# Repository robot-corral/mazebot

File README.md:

# mazebot
robot which sole purpose is to escape a maze

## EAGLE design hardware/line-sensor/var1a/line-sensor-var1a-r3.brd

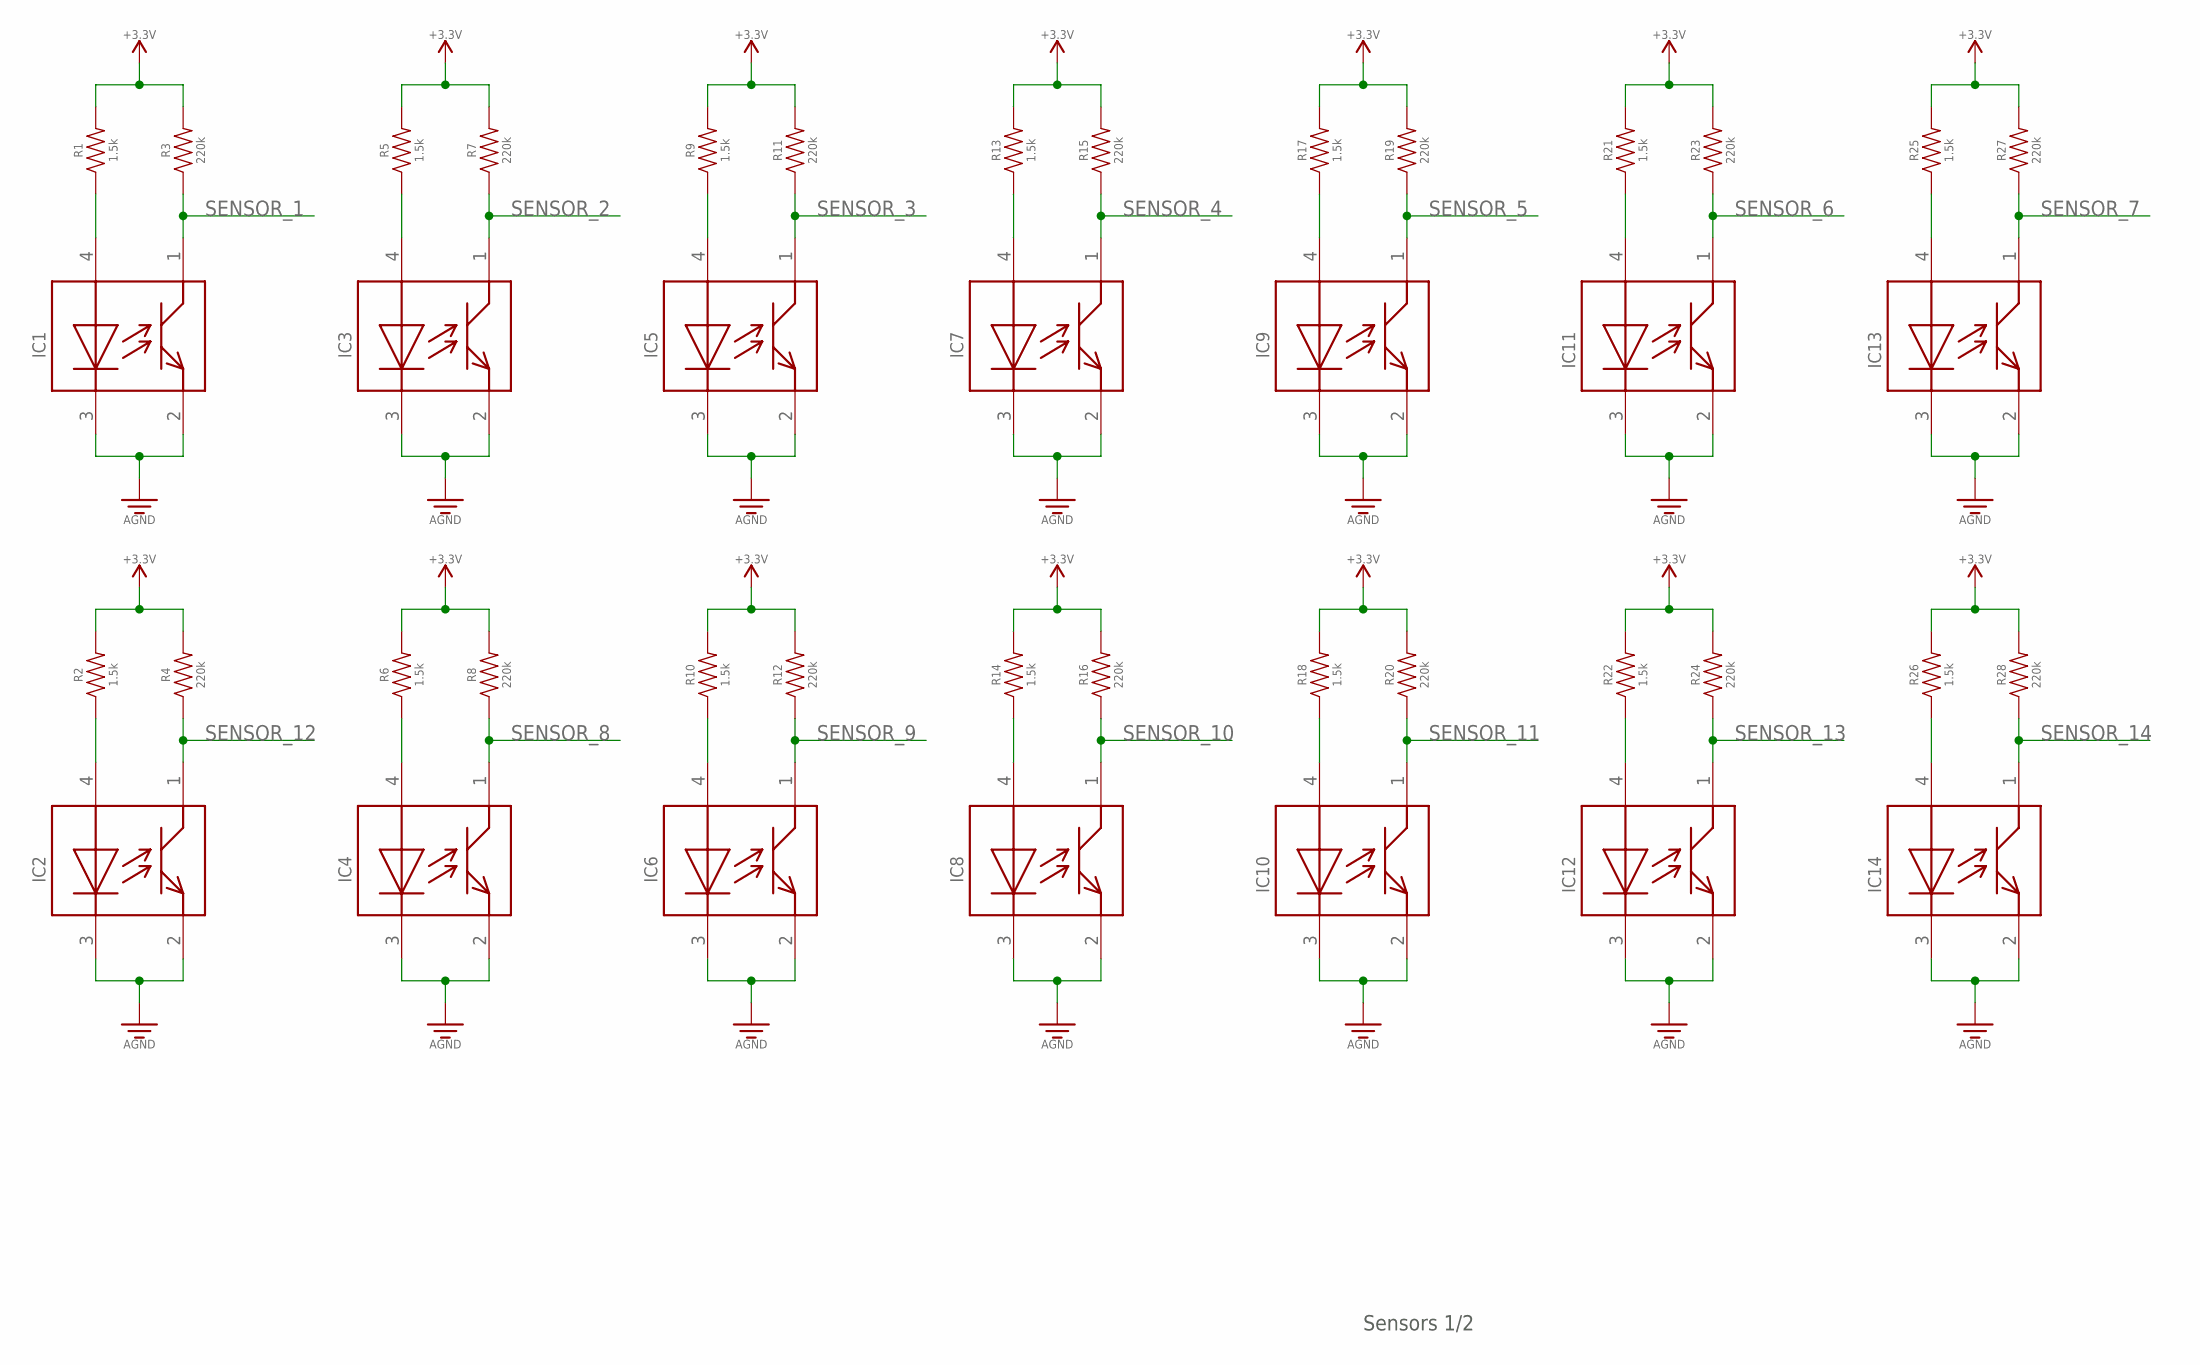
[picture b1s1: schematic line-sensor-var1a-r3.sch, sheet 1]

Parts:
IC1, IC2, IC3, IC4, IC5, IC6, IC7, IC8, IC9, IC10, IC11, IC12, IC13, IC14: GP2S60
R1, R2, R5, R6, R9, R10, R13, R14, R17, R18, R21, R22, R25, R26: 1.5k; RESISTOR-0603
R3, R4, R7, R8, R11, R12, R15, R16, R19, R20, R23, R24, R27, R28: 220k; RESISTOR-0603

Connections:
GND: IC1.2, IC1.3, IC2.2, IC2.3, IC3.2, IC3.3, IC4.2, IC4.3, IC5.2, IC5.3, IC6.2, IC6.3, IC7.2, IC7.3, IC8.2, IC8.3, IC9.2, IC9.3, IC10.2, IC10.3, IC11.2, IC11.3, IC12.2, IC12.3, IC13.2, IC13.3, IC14.2, IC14.3; also elsewhere on the board
unnamed: IC3.4, R5.P$1 (1)
unnamed: IC1.4, R1.P$1 (1)
unnamed: IC5.4, R9.P$1 (1)
unnamed: IC7.4, R13.P$1 (1)
unnamed: IC9.4, R17.P$1 (1)
unnamed: IC11.4, R21.P$1 (1)
unnamed: IC13.4, R25.P$1 (1)
unnamed: IC4.4, R6.P$1 (1)
unnamed: IC6.4, R10.P$1 (1)
unnamed: IC8.4, R14.P$1 (1)
unnamed: IC10.4, R18.P$1 (1)
unnamed: IC2.4, R2.P$1 (1)
unnamed: IC12.4, R22.P$1 (1)
unnamed: IC14.4, R26.P$1 (1)
SENSOR_1: IC1.1, R3.P$1 (1); also elsewhere on the board
SENSOR_2: IC3.1, R7.P$1 (1); also elsewhere on the board
SENSOR_3: IC5.1, R11.P$1 (1); also elsewhere on the board
SENSOR_4: IC7.1, R15.P$1 (1); also elsewhere on the board
SENSOR_5: IC9.1, R19.P$1 (1); also elsewhere on the board
SENSOR_6: IC11.1, R23.P$1 (1); also elsewhere on the board
SENSOR_7: IC13.1, R27.P$1 (1); also elsewhere on the board
SENSOR_8: IC4.1, R8.P$1 (1); also elsewhere on the board
SENSOR_9: IC6.1, R12.P$1 (1); also elsewhere on the board
SENSOR_10: IC8.1, R16.P$1 (1); also elsewhere on the board
SENSOR_11: IC10.1, R20.P$1 (1); also elsewhere on the board
SENSOR_12: IC2.1, R4.P$1 (1); also elsewhere on the board
SENSOR_13: IC12.1, R24.P$1 (1); also elsewhere on the board
SENSOR_14: IC14.1, R28.P$1 (1); also elsewhere on the board
VDD: R1.P$2 (2), R2.P$2 (2), R3.P$2 (2), R4.P$2 (2), R5.P$2 (2), R6.P$2 (2), R7.P$2 (2), R8.P$2 (2), R9.P$2 (2), R10.P$2 (2), R11.P$2 (2), R12.P$2 (2), R13.P$2 (2), R14.P$2 (2), R15.P$2 (2), R16.P$2 (2), R17.P$2 (2), R18.P$2 (2), R19.P$2 (2), R20.P$2 (2), R21.P$2 (2), R22.P$2 (2), R23.P$2 (2), R24.P$2 (2), R25.P$2 (2), R26.P$2 (2), R27.P$2 (2), R28.P$2 (2); also elsewhere on the board

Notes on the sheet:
Sensors 1/2

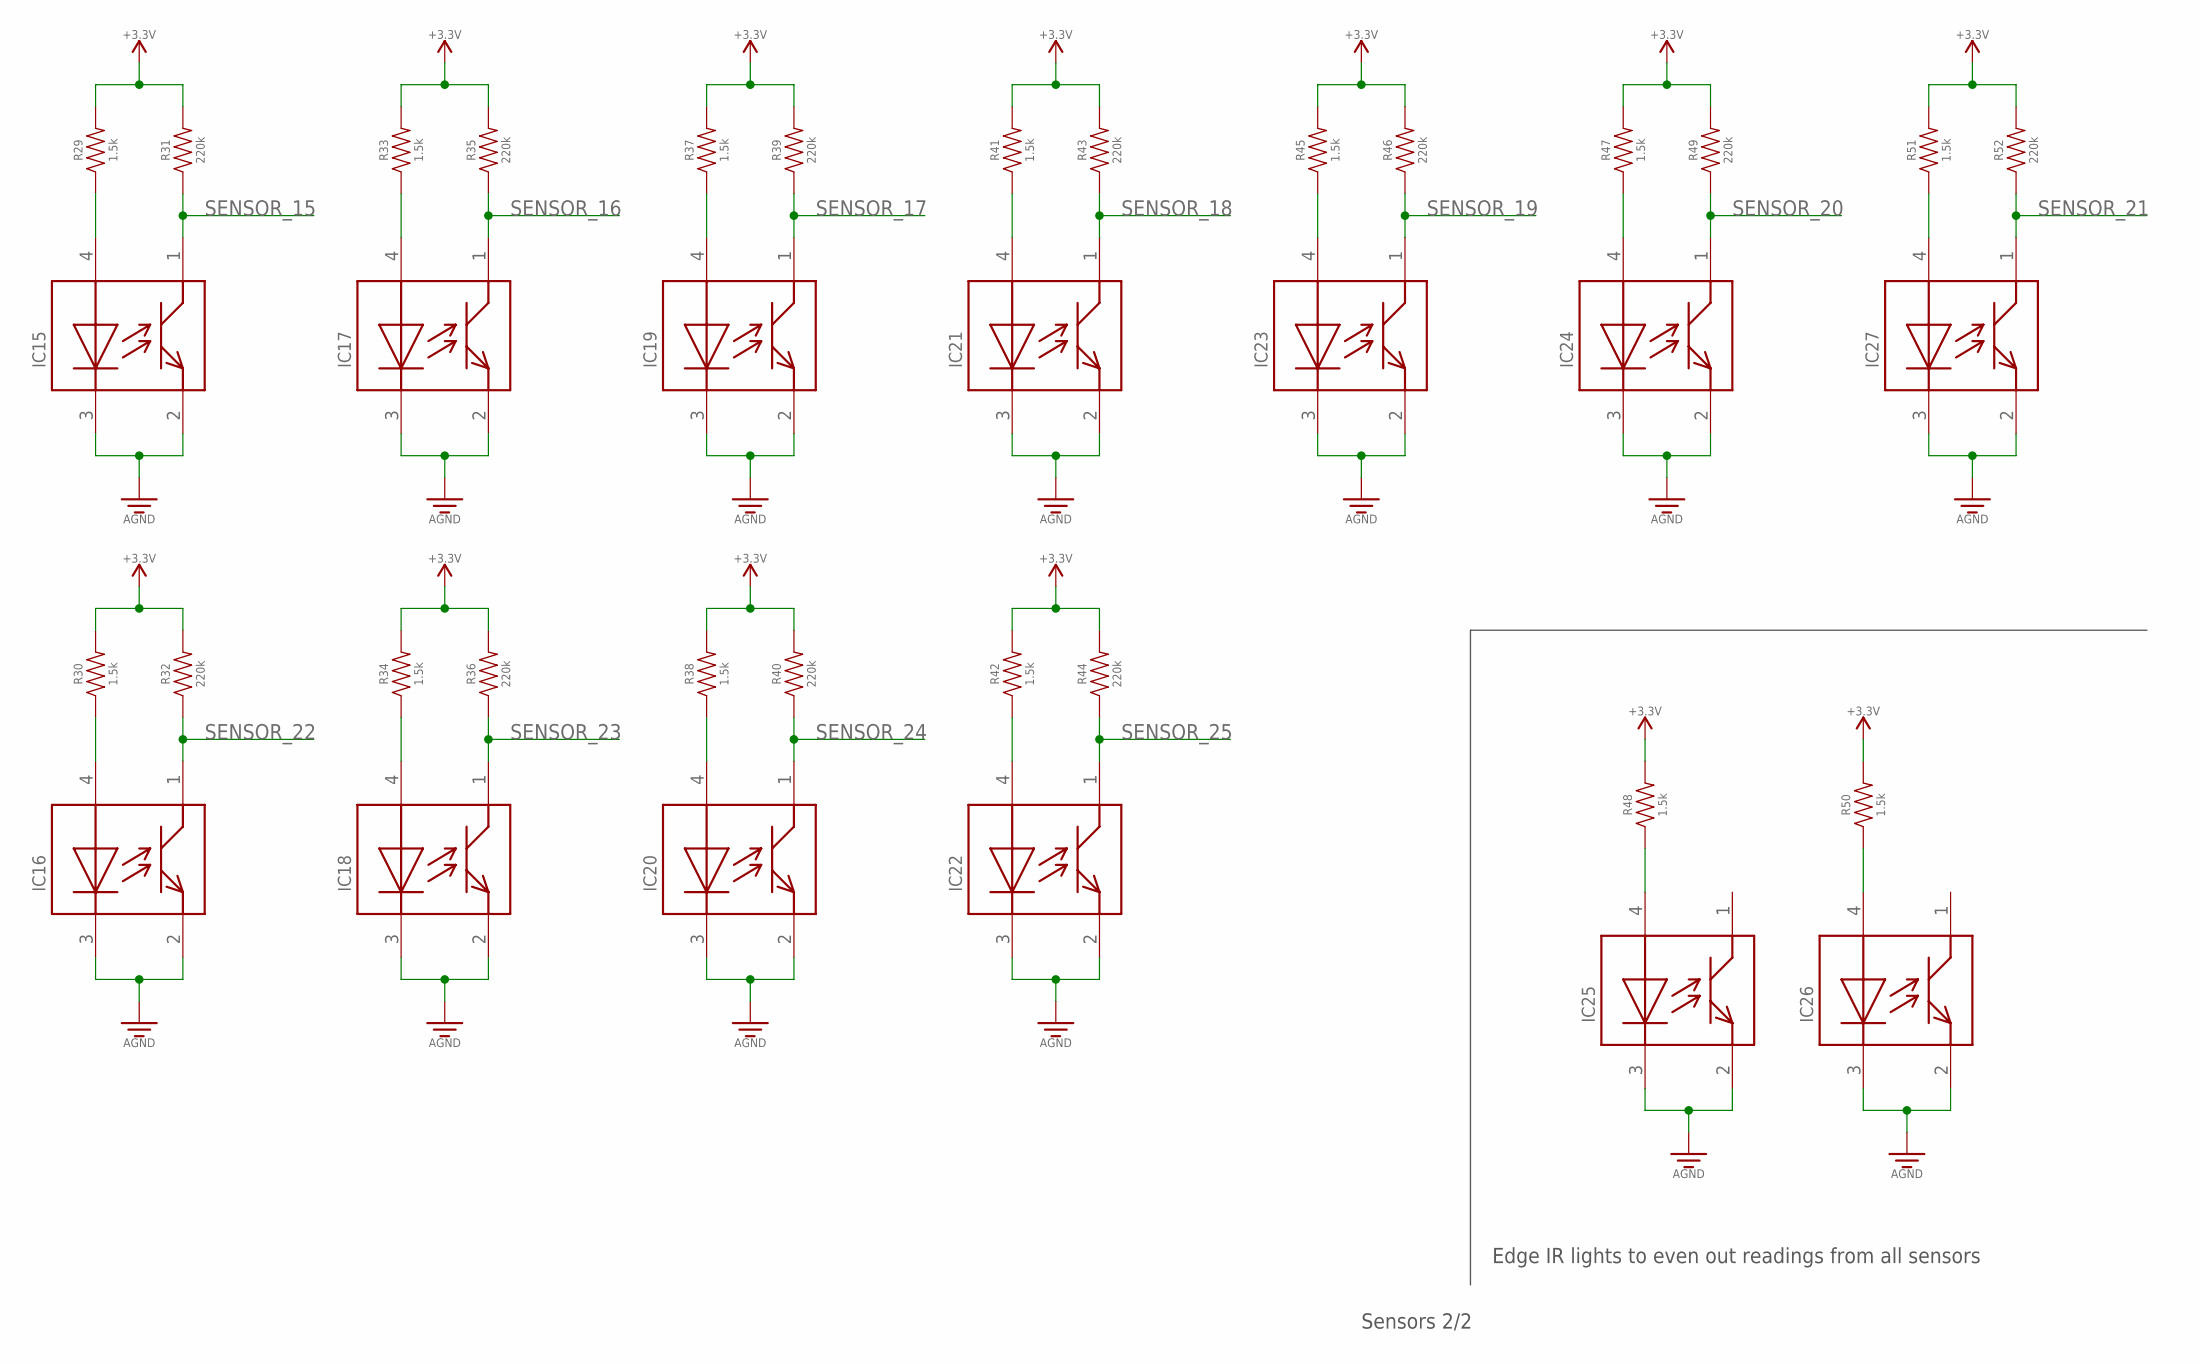
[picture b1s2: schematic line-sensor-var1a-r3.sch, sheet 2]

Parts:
IC15, IC16, IC17, IC18, IC19, IC20, IC21, IC22, IC23, IC24, IC25, IC26, IC27: GP2S60
R29, R30, R33, R34, R37, R38, R41, R42, R45, R47, R48, R50, R51: 1.5k; RESISTOR-0603
R31, R32, R35, R36, R39, R40, R43, R44, R46, R49, R52: 220k; RESISTOR-0603

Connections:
GND: IC15.2, IC15.3, IC16.2, IC16.3, IC17.2, IC17.3, IC18.2, IC18.3, IC19.2, IC19.3, IC20.2, IC20.3, IC21.2, IC21.3, IC22.2, IC22.3, IC23.2, IC23.3, IC24.2, IC24.3, IC25.2, IC25.3, IC26.2, IC26.3, IC27.2, IC27.3; also elsewhere on the board
unnamed: IC15.4, R29.P$1 (1)
unnamed: IC17.4, R33.P$1 (1)
unnamed: IC19.4, R37.P$1 (1)
unnamed: IC21.4, R41.P$1 (1)
unnamed: IC23.4, R45.P$1 (1)
unnamed: IC24.4, R47.P$1 (1)
unnamed: IC27.4, R51.P$1 (1)
unnamed: IC16.4, R30.P$1 (1)
unnamed: IC18.4, R34.P$1 (1)
unnamed: IC20.4, R38.P$1 (1)
unnamed: IC22.4, R42.P$1 (1)
unnamed: IC26.4, R50.P$1 (1)
unnamed: IC25.4, R48.P$1 (1)
SENSOR_15: IC15.1, R31.P$1 (1); also elsewhere on the board
SENSOR_16: IC17.1, R35.P$1 (1); also elsewhere on the board
SENSOR_17: IC19.1, R39.P$1 (1); also elsewhere on the board
SENSOR_18: IC21.1, R43.P$1 (1); also elsewhere on the board
SENSOR_19: IC23.1, R46.P$1 (1); also elsewhere on the board
SENSOR_20: IC24.1, R49.P$1 (1); also elsewhere on the board
SENSOR_21: IC27.1, R52.P$1 (1); also elsewhere on the board
SENSOR_22: IC16.1, R32.P$1 (1); also elsewhere on the board
SENSOR_23: IC18.1, R36.P$1 (1); also elsewhere on the board
SENSOR_24: IC20.1, R40.P$1 (1); also elsewhere on the board
SENSOR_25: IC22.1, R44.P$1 (1); also elsewhere on the board
VDD: R29.P$2 (2), R30.P$2 (2), R31.P$2 (2), R32.P$2 (2), R33.P$2 (2), R34.P$2 (2), R35.P$2 (2), R36.P$2 (2), R37.P$2 (2), R38.P$2 (2), R39.P$2 (2), R40.P$2 (2), R41.P$2 (2), R42.P$2 (2), R43.P$2 (2), R44.P$2 (2), R45.P$2 (2), R46.P$2 (2), R47.P$2 (2), R48.P$2 (2), R49.P$2 (2), R50.P$2 (2), R51.P$2 (2), R52.P$2 (2); also elsewhere on the board

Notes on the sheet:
Sensors 2/2
Edge IR lights to even out readings from all sensors

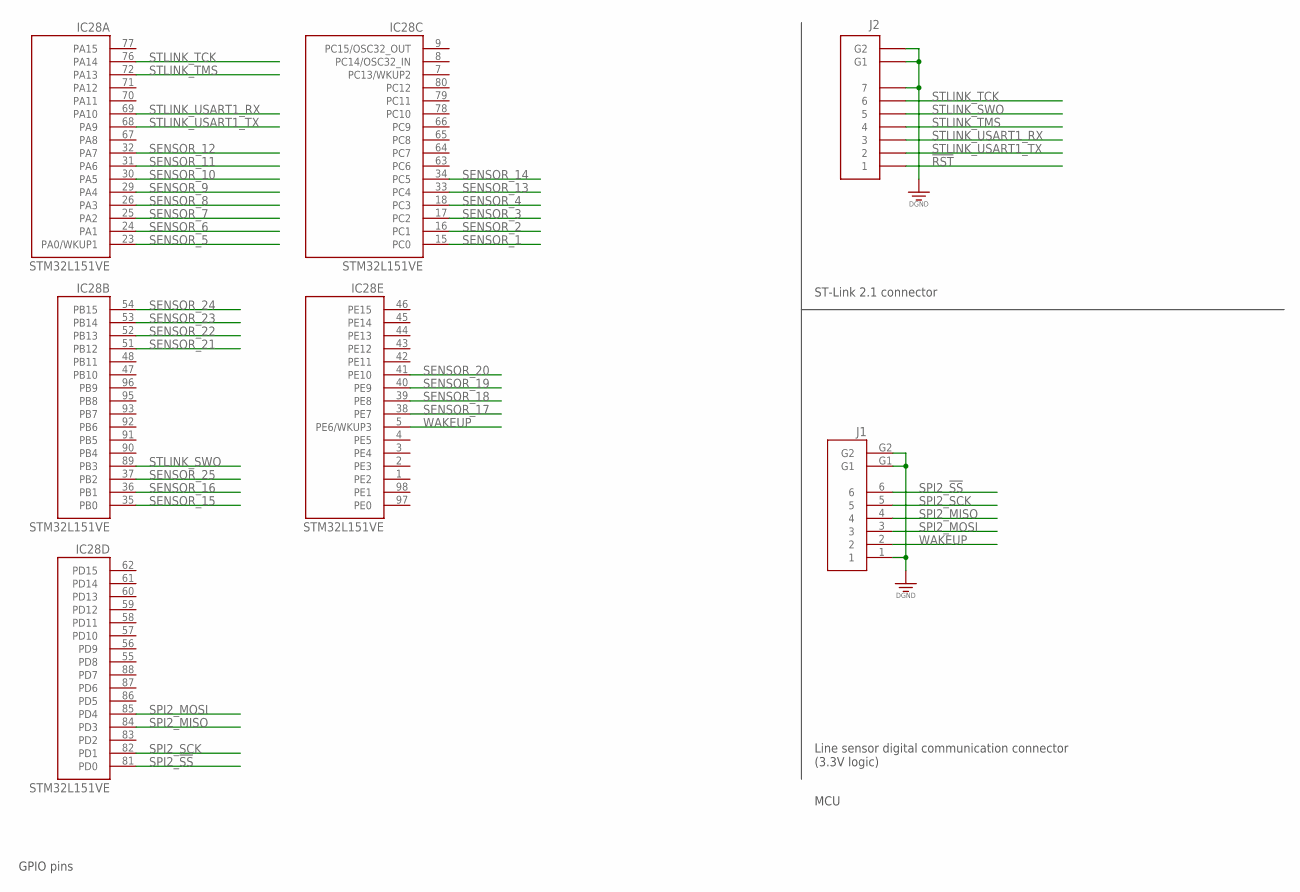
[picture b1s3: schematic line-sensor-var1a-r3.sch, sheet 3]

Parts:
IC28: STM32L151VE; LQFP100_14X14
J1: MOLEX-502382-06XX
J2: MOLEX-53261-0771

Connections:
!RST: J2.1; also elsewhere on the board
GND: J1.1, J1.G1, J1.G2, J2.7, J2.G1, J2.G2; also elsewhere on the board
SENSOR_1: IC28.15 (PC0); also elsewhere on the board
SENSOR_2: IC28.16 (PC1); also elsewhere on the board
SENSOR_3: IC28.17 (PC2); also elsewhere on the board
SENSOR_4: IC28.18 (PC3); also elsewhere on the board
SENSOR_5: IC28.23 (PA0/WKUP1); also elsewhere on the board
SENSOR_6: IC28.24 (PA1); also elsewhere on the board
SENSOR_7: IC28.25 (PA2); also elsewhere on the board
SENSOR_8: IC28.26 (PA3); also elsewhere on the board
SENSOR_9: IC28.29 (PA4); also elsewhere on the board
SENSOR_10: IC28.30 (PA5); also elsewhere on the board
SENSOR_11: IC28.31 (PA6); also elsewhere on the board
SENSOR_12: IC28.32 (PA7); also elsewhere on the board
SENSOR_13: IC28.33 (PC4); also elsewhere on the board
SENSOR_14: IC28.34 (PC5); also elsewhere on the board
SENSOR_15: IC28.35 (PB0); also elsewhere on the board
SENSOR_16: IC28.36 (PB1); also elsewhere on the board
SENSOR_17: IC28.38 (PE7); also elsewhere on the board
SENSOR_18: IC28.39 (PE8); also elsewhere on the board
SENSOR_19: IC28.40 (PE9); also elsewhere on the board
SENSOR_20: IC28.41 (PE10); also elsewhere on the board
SENSOR_21: IC28.51 (PB12); also elsewhere on the board
SENSOR_22: IC28.52 (PB13); also elsewhere on the board
SENSOR_23: IC28.53 (PB14); also elsewhere on the board
SENSOR_24: IC28.54 (PB15); also elsewhere on the board
SENSOR_25: IC28.37 (PB2); also elsewhere on the board
SPI2_!SS: IC28.81 (PD0), J1.6
SPI2_MISO: IC28.84 (PD3), J1.4
SPI2_MOSI: IC28.85 (PD4), J1.3
SPI2_SCK: IC28.82 (PD1), J1.5
STLINK_SWO: IC28.89 (PB3), J2.5
STLINK_TCK: IC28.76 (PA14), J2.6
STLINK_TMS: IC28.72 (PA13), J2.4
STLINK_USART1_RX: IC28.69 (PA10), J2.3
STLINK_USART1_TX: IC28.68 (PA9), J2.2
WAKEUP: IC28.5 (PE6/WKUP3), J1.2

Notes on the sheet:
MCU
GPIO pins
ST-Link 2.1 connector
Line sensor digital communication connector (3.3V logic)

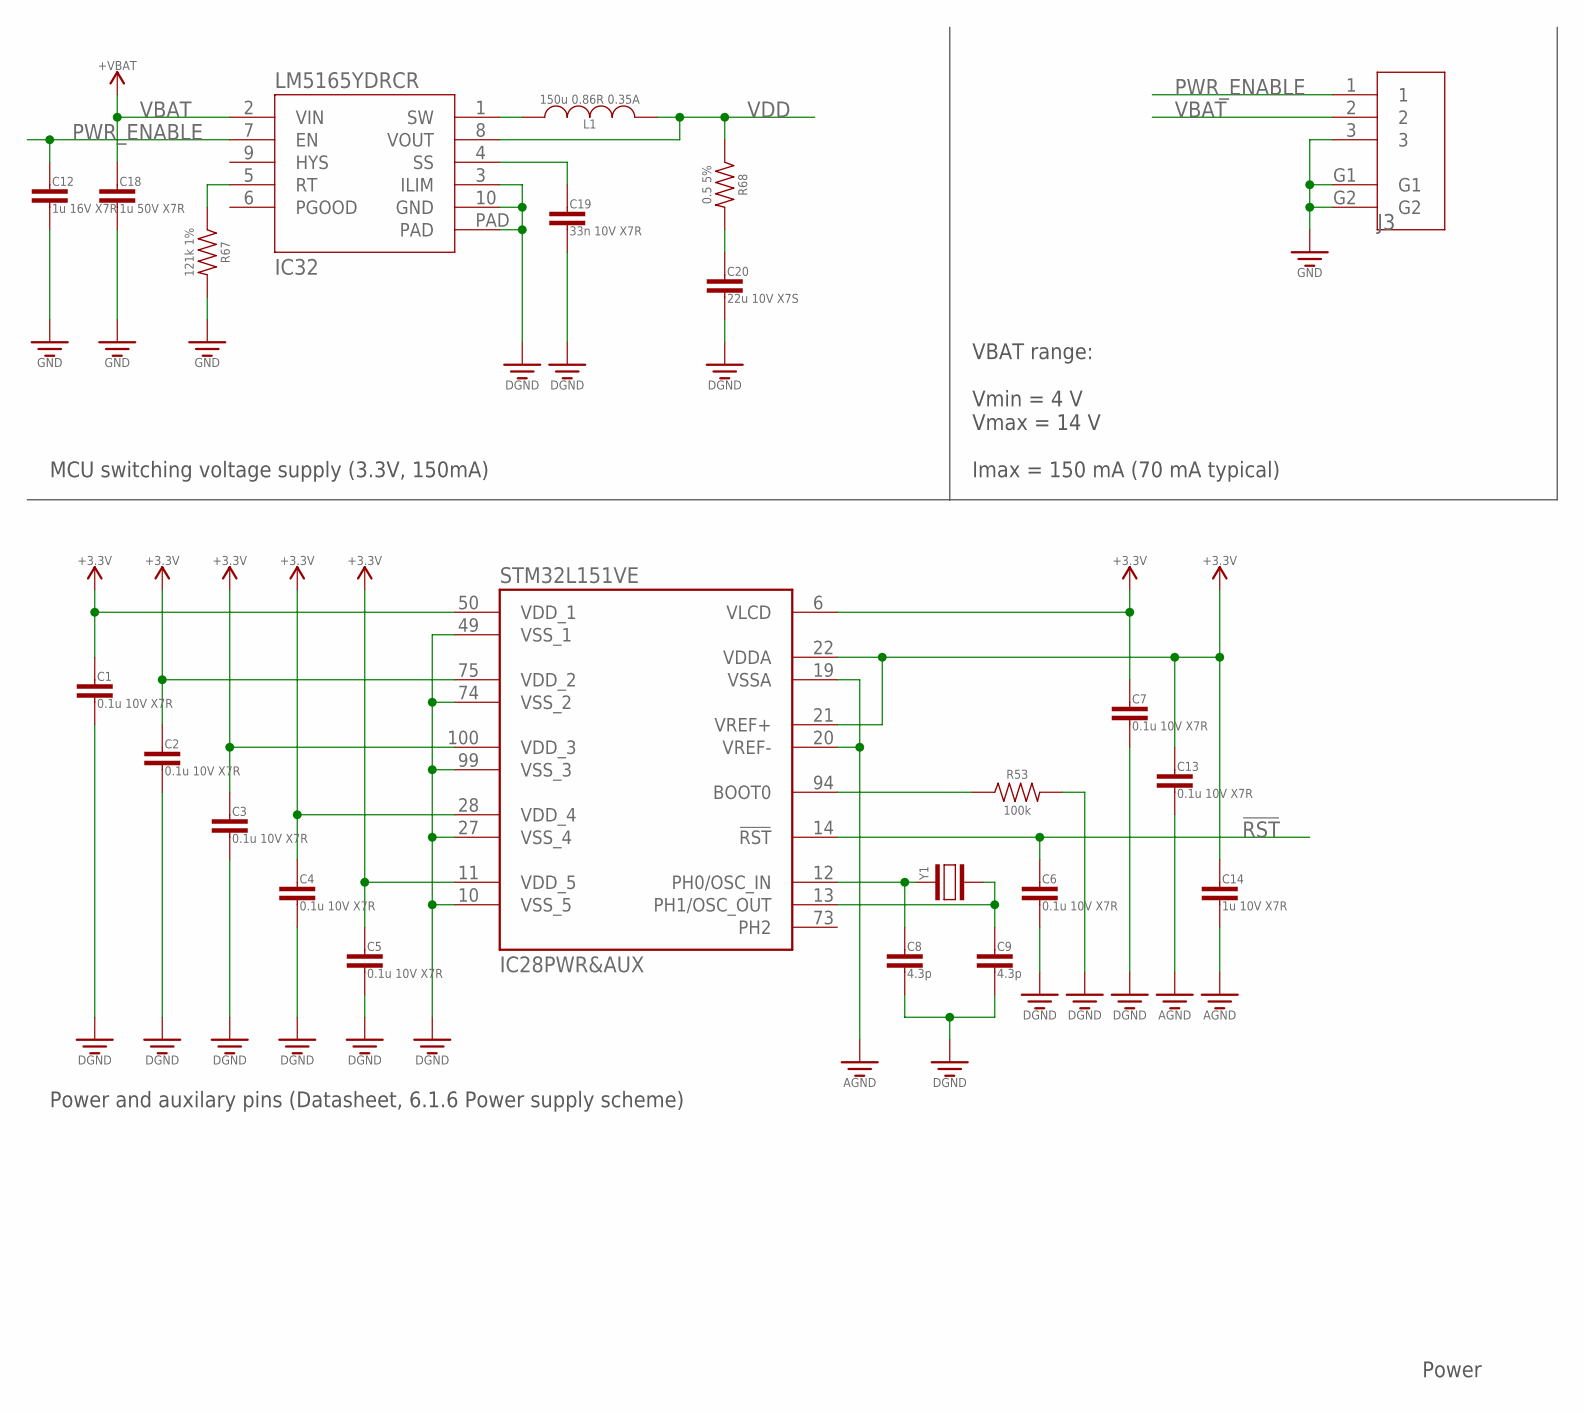
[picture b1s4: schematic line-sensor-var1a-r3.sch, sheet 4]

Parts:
C1, C2, C3, C4, C5, C6, C7, C13: 0.1u 10V X7R; CAPACITOR-0402
C8, C9: 4.3p; CAPACITOR-0603
C12: 1u 16V X7R; CAPACITOR-0603
C14: 1u 10V X7R; CAPACITOR-0402
C18: 1u 50V X7R; CAPACITOR-1206
C19: 33n 10V X7R; CAPACITOR-0603
C20: 22u 10V X7S; CAPACITOR-0805
IC28: STM32L151VE; LQFP100_14X14
IC32: LM5165YDRCR; VSON-10-0.5MM
J3: MOLEX-502382-03XX
L1: 150u 0.86R 0.35A; PANASONIC-SERIES-H
R53: 100k; RESISTOR-0603
R67: 121k 1%; RESISTOR-0603
R68: 0.5 5%; RESISTOR-0603
Y1: CRYSTALKYOCERA-CX5032GA; KYOCERA-CX5032GA

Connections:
!RST: C6.P$1 (1), IC28.14 (!RST!); also elsewhere on the board
BOOT0: IC28.94 (BOOT0), R53.P$1 (1)
GND: C1.P$2 (2), C2.P$2 (2), C3.P$2 (2), C4.P$2 (2), C5.P$2 (2), C6.P$2 (2), C7.P$2 (2), C8.2, C9.2, C12.2, C13.P$2 (2), C14.P$2 (2), C18.P$2 (2), C19.2, C20.2, IC28.10 (VSS_5), IC28.19 (VSSA), IC28.20 (VREF-), IC28.27 (VSS_4), IC28.49 (VSS_1), IC28.74 (VSS_2), IC28.99 (VSS_3), IC32.3 (ILIM), IC32.10 (GND), IC32.PAD, J3.3, J3.G1, J3.G2, R53.P$2 (2), R67.P$2 (2); also elsewhere on the board
IC32_SW: IC32.1 (SW), L1.1
unnamed: C8.1, IC28.12 (PH0/OSC_IN), Y1.P$1 (1)
unnamed: C9.1, IC28.13 (PH1/OSC_OUT), Y1.P$2 (2)
unnamed: IC32.5 (RT), R67.P$1 (1)
unnamed: C19.1, IC32.4 (SS)
unnamed: C20.1, R68.P$2 (2)
PWR_ENABLE: C12.1, IC32.7 (EN), J3.1
VBAT: C18.P$1 (1), IC32.2 (VIN), J3.2
VDD: C1.P$1 (1), C2.P$1 (1), C3.P$1 (1), C4.P$1 (1), C5.P$1 (1), C7.P$1 (1), C13.P$1 (1), C14.P$1 (1), IC28.6 (VLCD), IC28.11 (VDD_5), IC28.21 (VREF+), IC28.22 (VDDA), IC28.28 (VDD_4), IC28.50 (VDD_1), IC28.75 (VDD_2), IC28.100 (VDD_3), IC32.8 (VOUT), L1.2, R68.P$1 (1); also elsewhere on the board

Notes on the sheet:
Power
VBAT range: Vmin = 4 V Vmax = 14 V Imax = 150 mA (70 mA typical)
MCU switching voltage supply (3.3V, 150mA)
Power and auxilary pins (Datasheet, 6.1.6 Power supply scheme)

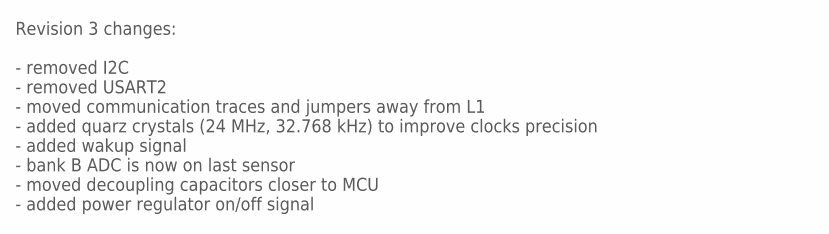
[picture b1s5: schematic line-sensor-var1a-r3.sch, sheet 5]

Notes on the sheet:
Revision 3 changes: - removed I2C - removed USART2 - moved communication traces and jumpers away from L1 - added quarz crystals (24 MHz, 32.768 kHz) to improve clocks precision - added wakup signal - bank B ADC is now on last sensor - moved decoupling capacitors closer to MCU - added power regulato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

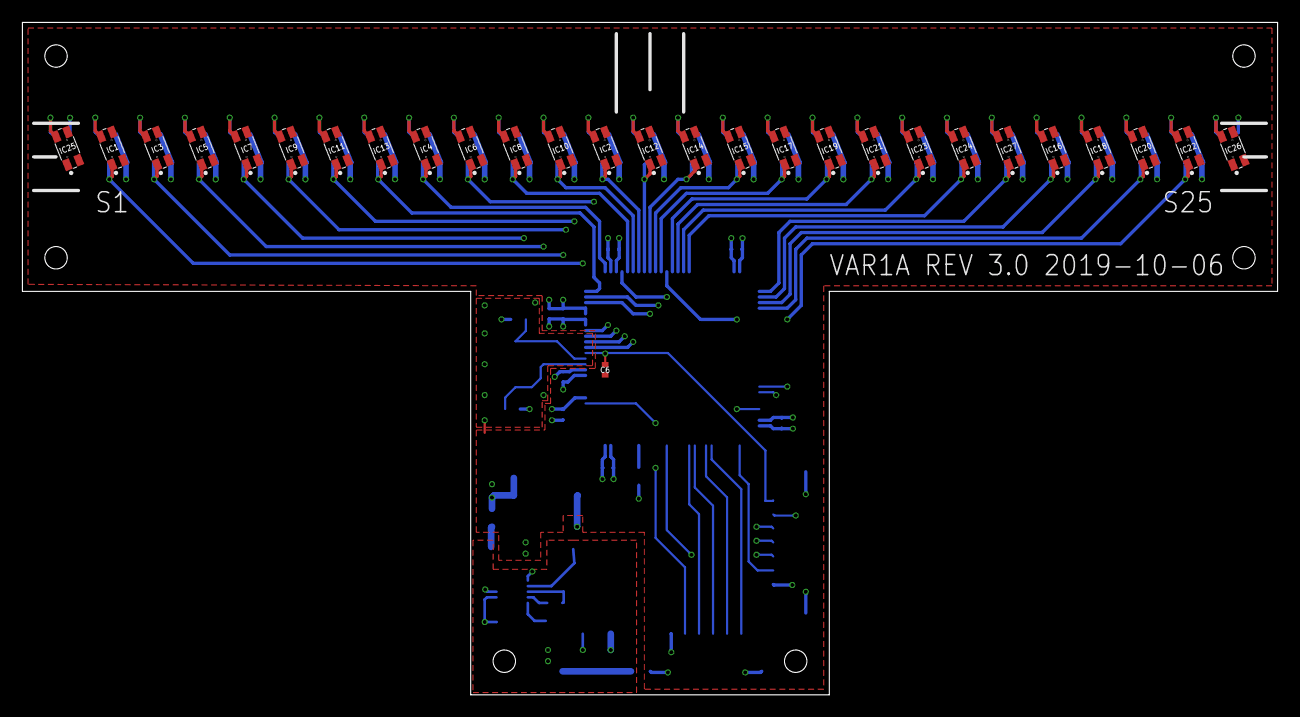
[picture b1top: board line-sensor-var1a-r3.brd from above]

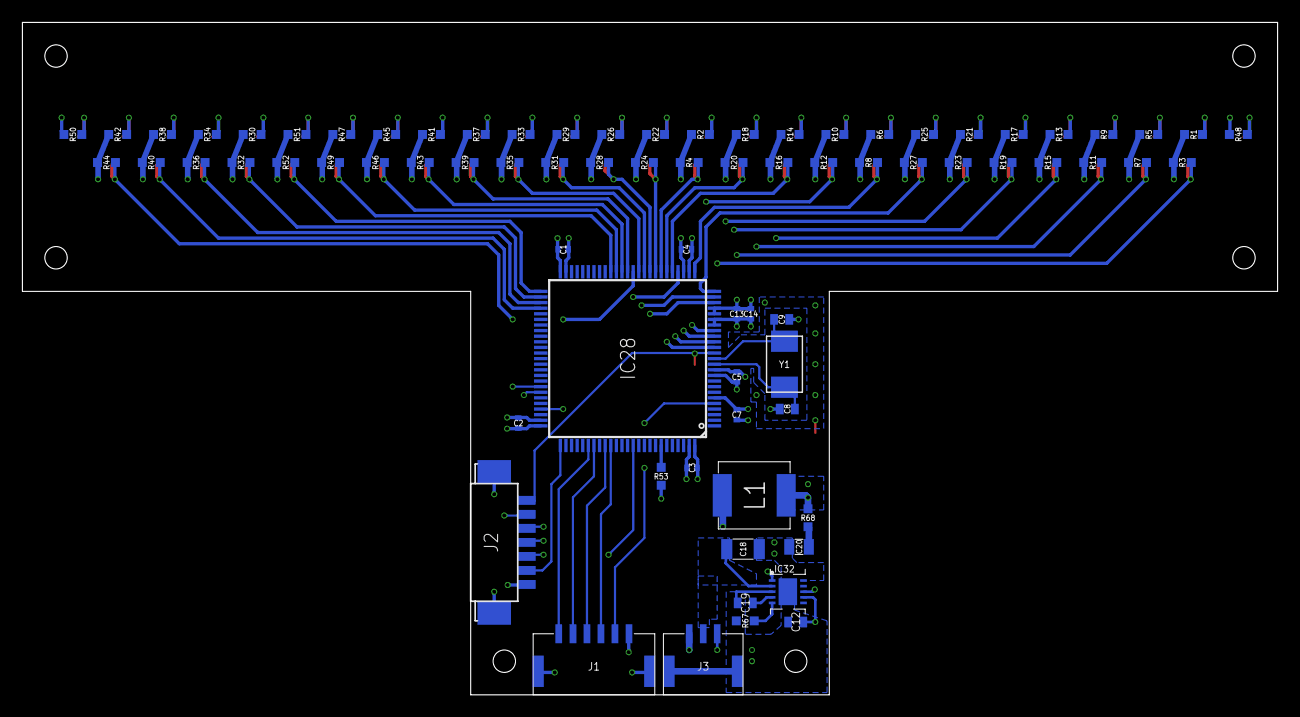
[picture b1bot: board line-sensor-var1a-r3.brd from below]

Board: 4 copper layers, 112.0 x 60.0 mm, 104 parts (76 on the bottom side), 74 nets.

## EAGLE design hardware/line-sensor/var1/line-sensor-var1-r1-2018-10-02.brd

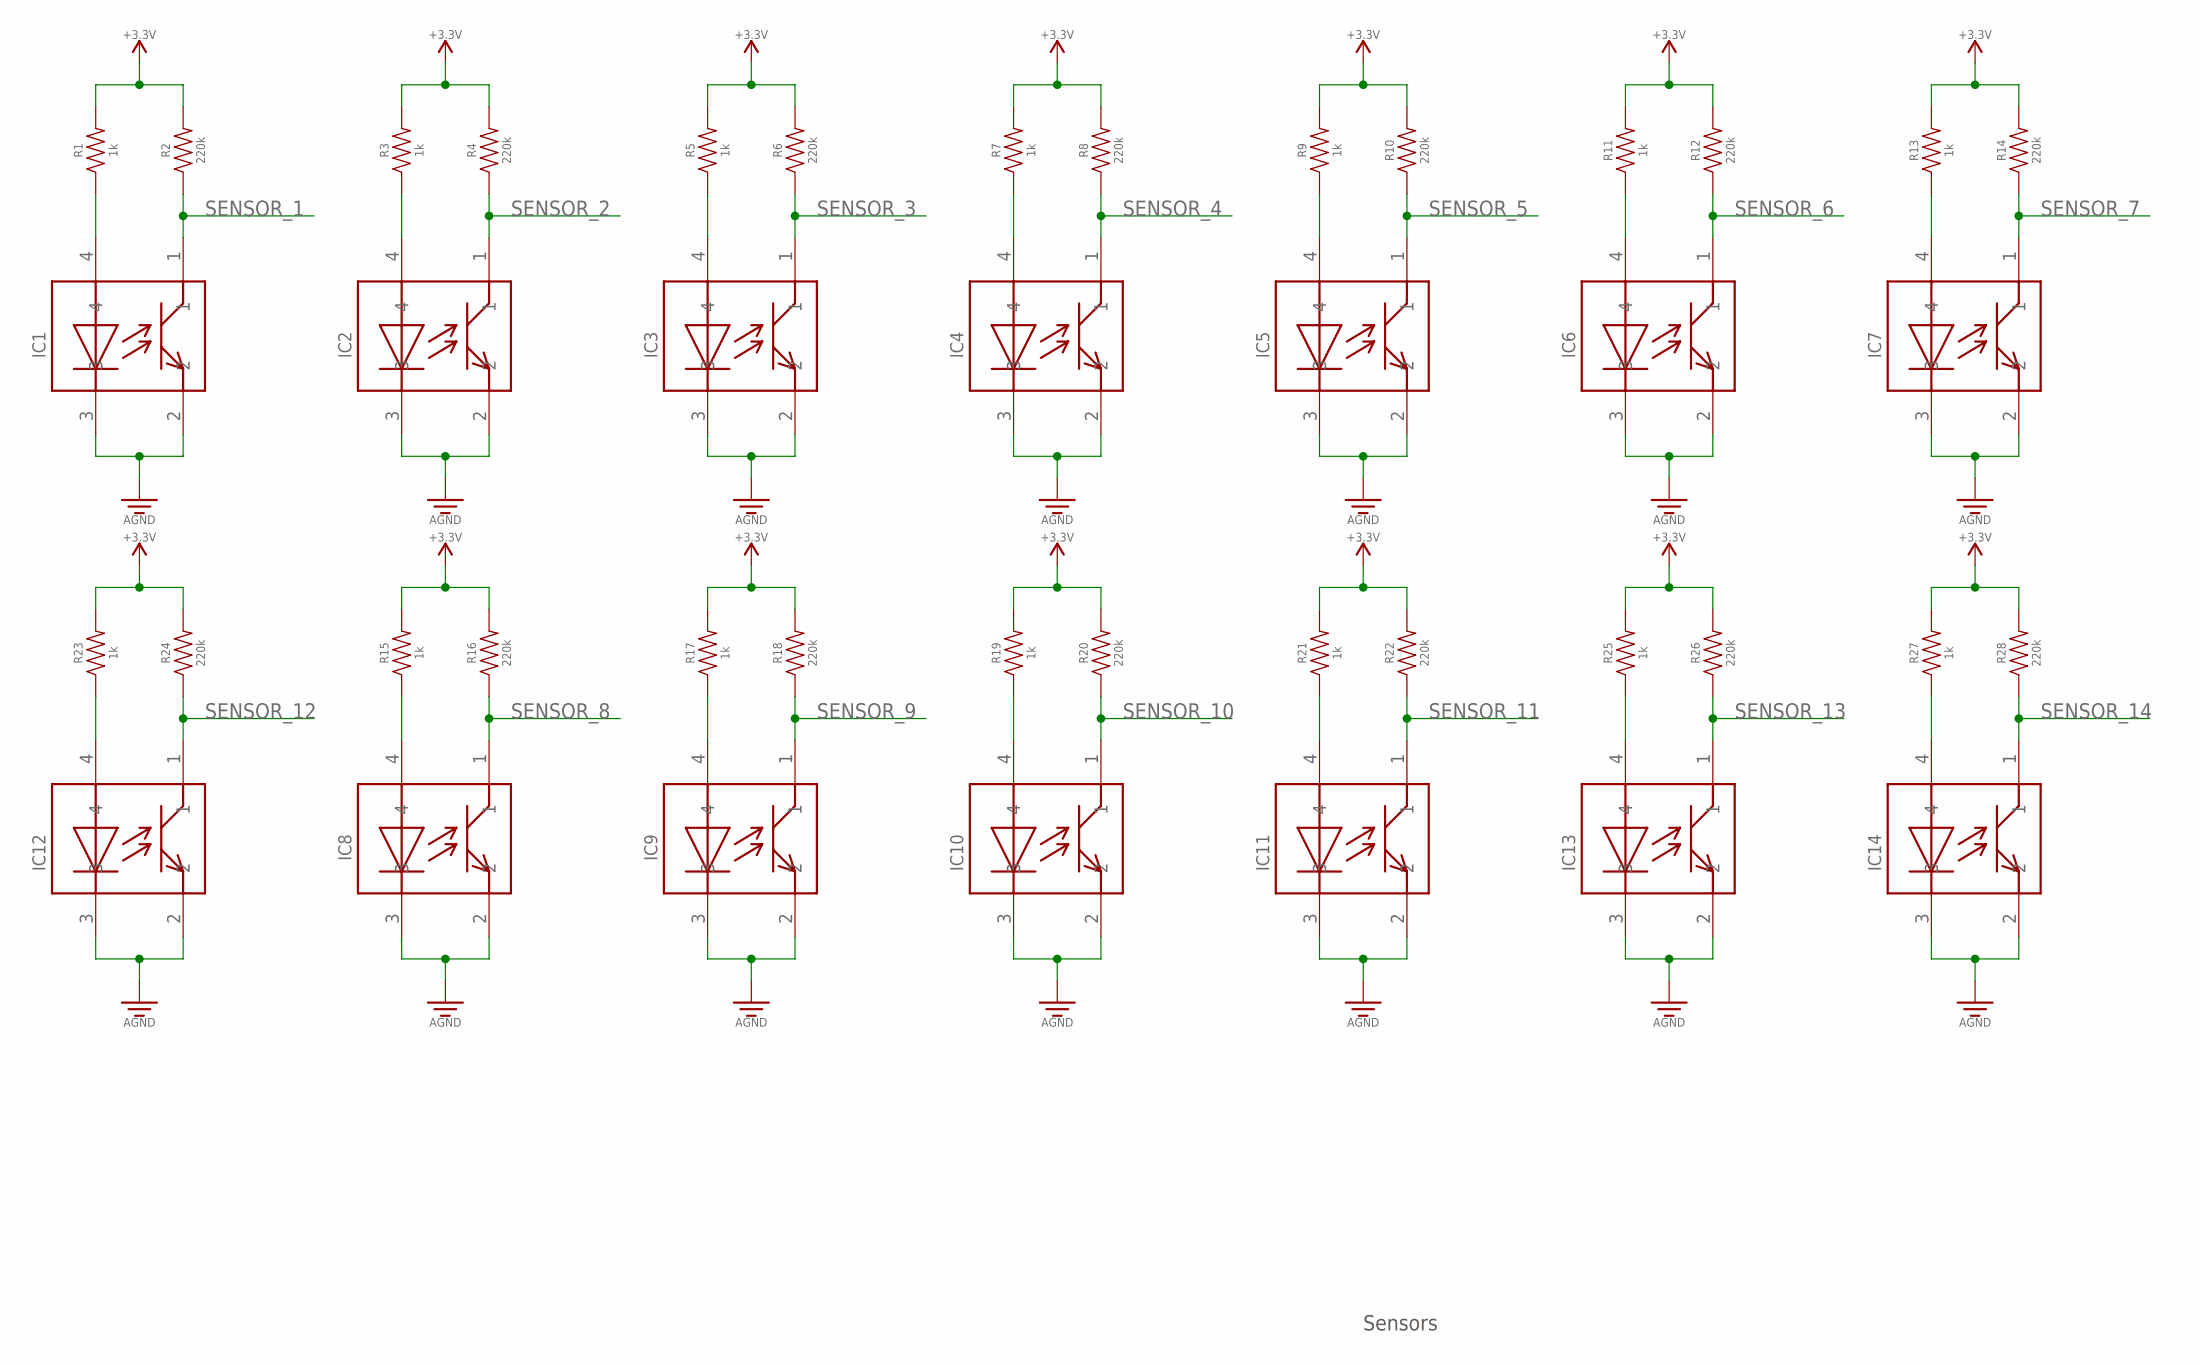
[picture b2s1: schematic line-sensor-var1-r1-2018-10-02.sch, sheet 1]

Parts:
IC1, IC2, IC3, IC4, IC5, IC6, IC7, IC8, IC9, IC10, IC11, IC12, IC13, IC14: GP2S60
R1, R3, R5, R7, R9, R11, R13, R15, R17, R19, R21, R23, R25, R27: 1k; RESISTOR-0603
R2, R4, R6, R8, R10, R12, R14, R16, R18, R20, R22, R24, R26, R28: 220k; RESISTOR-0603

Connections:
3V3: R1.P$2 (2), R2.P$2 (2), R3.P$2 (2), R4.P$2 (2), R5.P$2 (2), R6.P$2 (2), R7.P$2 (2), R8.P$2 (2), R9.P$2 (2), R10.P$2 (2), R11.P$2 (2), R12.P$2 (2), R13.P$2 (2), R14.P$2 (2), R15.P$2 (2), R16.P$2 (2), R17.P$2 (2), R18.P$2 (2), R19.P$2 (2), R20.P$2 (2), R21.P$2 (2), R22.P$2 (2), R23.P$2 (2), R24.P$2 (2), R25.P$2 (2), R26.P$2 (2), R27.P$2 (2), R28.P$2 (2); also elsewhere on the board
AGND: IC1.2, IC1.3, IC2.2, IC2.3, IC3.2, IC3.3, IC4.2, IC4.3, IC5.2, IC5.3, IC6.2, IC6.3, IC7.2, IC7.3, IC8.2, IC8.3, IC9.2, IC9.3, IC10.2, IC10.3, IC11.2, IC11.3, IC12.2, IC12.3, IC13.2, IC13.3, IC14.2, IC14.3; also elsewhere on the board
unnamed: IC2.4, R3.P$1 (1)
unnamed: IC1.4, R1.P$1 (1)
unnamed: IC3.4, R5.P$1 (1)
unnamed: IC4.4, R7.P$1 (1)
unnamed: IC5.4, R9.P$1 (1)
unnamed: IC6.4, R11.P$1 (1)
unnamed: IC7.4, R13.P$1 (1)
unnamed: IC8.4, R15.P$1 (1)
unnamed: IC9.4, R17.P$1 (1)
unnamed: IC10.4, R19.P$1 (1)
unnamed: IC11.4, R21.P$1 (1)
unnamed: IC12.4, R23.P$1 (1)
unnamed: IC13.4, R25.P$1 (1)
unnamed: IC14.4, R27.P$1 (1)
SENSOR_1: IC1.1, R2.P$1 (1); also elsewhere on the board
SENSOR_2: IC2.1, R4.P$1 (1); also elsewhere on the board
SENSOR_3: IC3.1, R6.P$1 (1); also elsewhere on the board
SENSOR_4: IC4.1, R8.P$1 (1); also elsewhere on the board
SENSOR_5: IC5.1, R10.P$1 (1); also elsewhere on the board
SENSOR_6: IC6.1, R12.P$1 (1); also elsewhere on the board
SENSOR_7: IC7.1, R14.P$1 (1); also elsewhere on the board
SENSOR_8: IC8.1, R16.P$1 (1); also elsewhere on the board
SENSOR_9: IC9.1, R18.P$1 (1); also elsewhere on the board
SENSOR_10: IC10.1, R20.P$1 (1); also elsewhere on the board
SENSOR_11: IC11.1, R22.P$1 (1); also elsewhere on the board
SENSOR_12: IC12.1, R24.P$1 (1); also elsewhere on the board
SENSOR_13: IC13.1, R26.P$1 (1); also elsewhere on the board
SENSOR_14: IC14.1, R28.P$1 (1); also elsewhere on the board

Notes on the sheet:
Sensors
